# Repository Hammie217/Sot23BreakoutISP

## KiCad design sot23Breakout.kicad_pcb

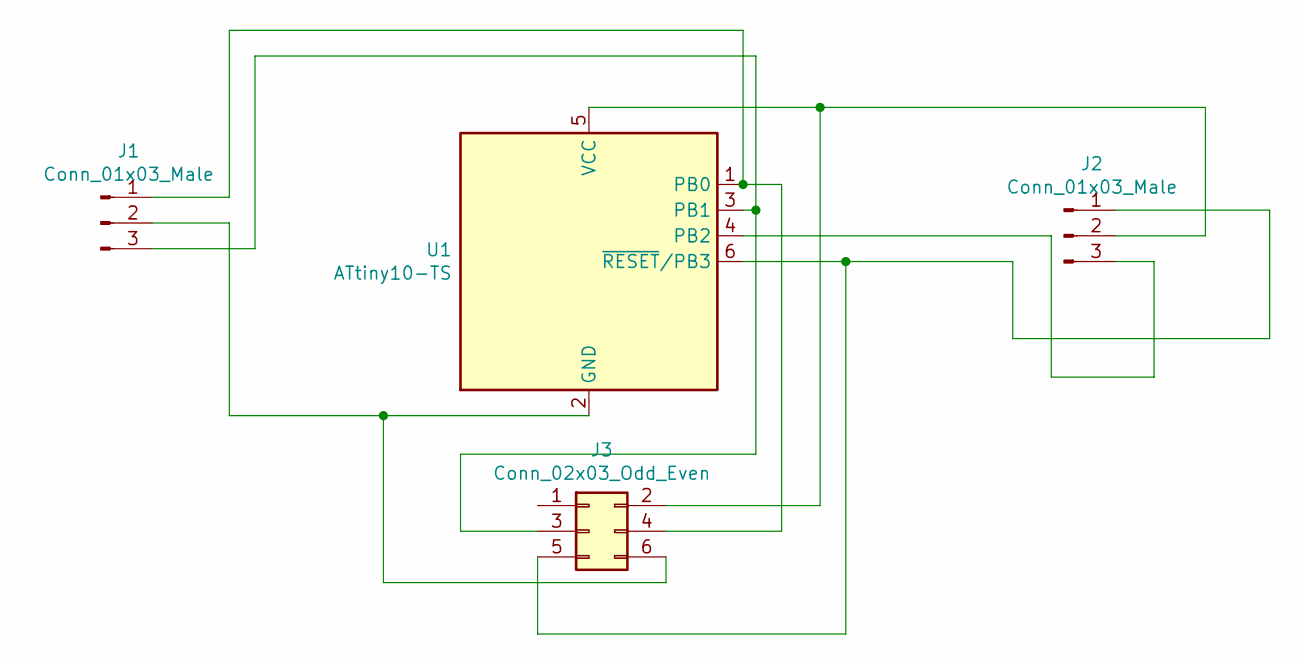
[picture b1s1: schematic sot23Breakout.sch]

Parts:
J1, J2: Conn_01x03_Male; PinHeader_1x03_P2.54mm_Vertical
J3: Conn_02x03_Odd_Even; PinHeader_2x03_P2.54mm_Vertical
U1: ATtiny10-TS; SOT-23-6

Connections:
unnamed: J1.1, J3.4, U1.1 (PB0)
unnamed: J1.2, J3.6, U1.2 (GND)
unnamed: J1.3, J3.3, U1.3 (PB1)
unnamed: J2.1, J3.5, U1.6 (~RESET~/PB3)
unnamed: J2.2, J3.2, U1.5 (VCC)
unnamed: J2.3, U1.4 (PB2)

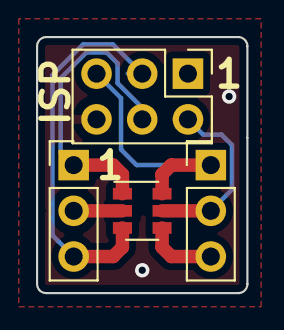
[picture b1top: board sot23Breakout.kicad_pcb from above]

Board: 2 copper layers, 11.7 x 14.2 mm, 4 parts (0 on the bottom side), 6 nets.
